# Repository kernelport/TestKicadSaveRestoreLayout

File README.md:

# TestKicadSaveRestoreLayout
Simple test restore 2 Layer Layout in a new Kicad Project

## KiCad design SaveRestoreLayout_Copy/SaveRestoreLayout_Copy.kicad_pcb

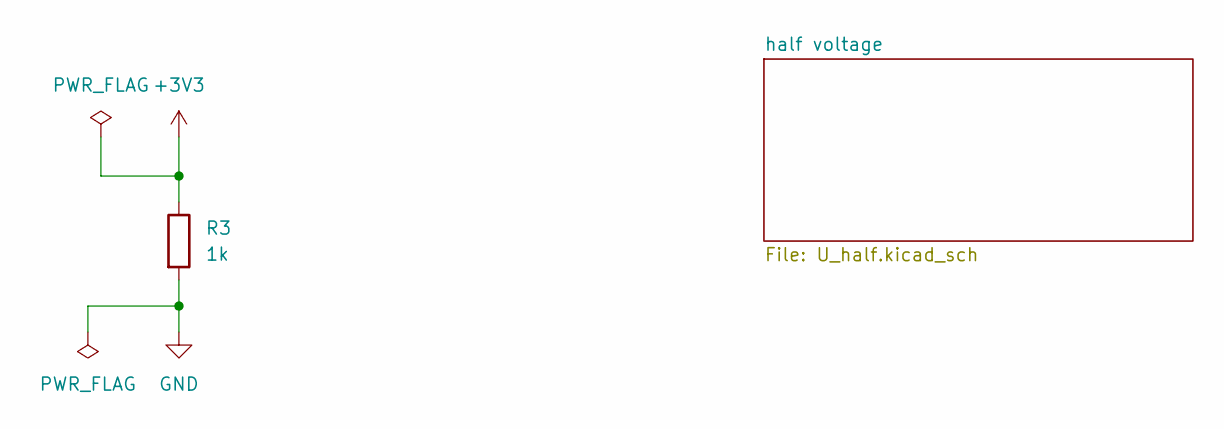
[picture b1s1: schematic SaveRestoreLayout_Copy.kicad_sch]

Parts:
R3: 1k; R_0603_1608Metric

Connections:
+3V3: R3.1; also elsewhere on the board
GND: R3.2; also elsewhere on the board

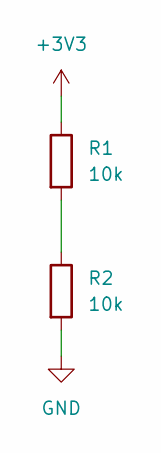
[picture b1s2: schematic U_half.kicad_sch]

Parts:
R1, R2: 10k; R_0603_1608Metric

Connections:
+3V3: R1.1; also elsewhere on the board
GND: R2.2; also elsewhere on the board
unnamed: R1.2, R2.1

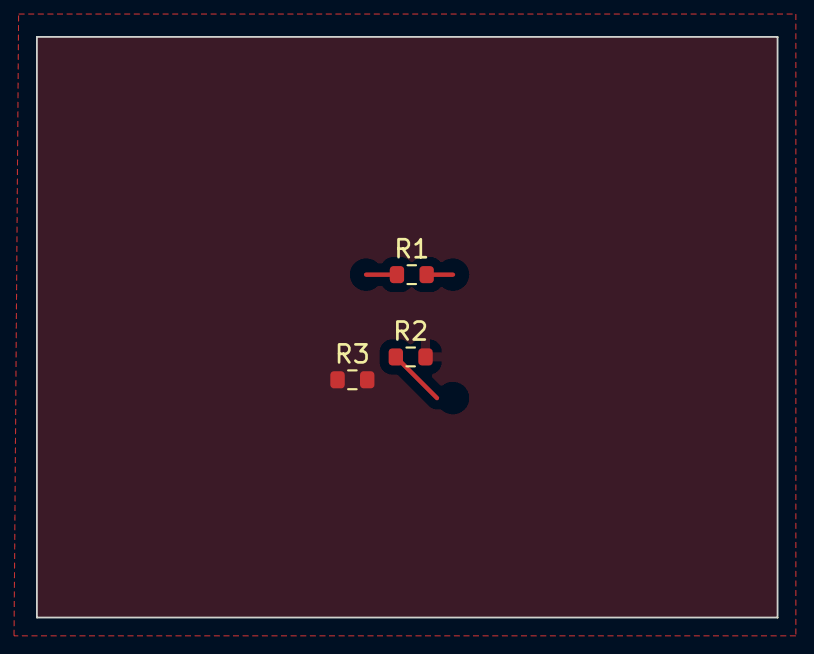
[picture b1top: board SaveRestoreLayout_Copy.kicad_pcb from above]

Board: 2 copper layers, 41.1 x 32.3 mm, 3 parts (0 on the bottom side), 3 nets.

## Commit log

2023-09-07 add SaveRestoreLayout_Original
2023-09-07 add .gitignore
2023-09-07 add new and empty SaveRestoreLayout_Copy
2023-09-07 copy and annotate SaveRestoreLayout_Copy/U_half.kicad_sch from SaveRestoreLayout_Original/U_half.kicad_sch
2023-09-07 save layout incl. intersecting
2023-09-07 copy the U_half.kicad_sch again after annotation in original
2023-09-07 annotate the copy of SaveRestoreLayout_Copy/U_half.kicad_sch
2023-09-07 restore the layour from original
    bug: the bottom layout is not restored and no via is placed
